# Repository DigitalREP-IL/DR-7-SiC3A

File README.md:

The Raspberry Pi, while a very capable and useful single-board computer, is often used with less than ideal power supplies. The Raspberry Pi monitors the incoming power and can both warn the user and slow down the system (clock throttling) to reduce power consumption. It is very common to have issues with SD Card corruption that can be traced back to power input issues as well. The simple solution presented by many kit vendors is to supply a power supply that provides 5.1V rather than the 5.0V nominal, in hopes that the extra voltage compensates for resistive losses in the cabling and by providing additional headroom over the 4.63V undervoltage warning level. However, a large contingent of would-be makers simply use a cellular phone charger and hope for the best. On older models, the power draw was somewhat lower but as of the latest 3B and 4 models the recommended supply current has risen to 3A.  Additionally, most USB chargers perform poorly at higher loads and may even drop out, hiccupping power to the SBC.

With this in mind, we’ve designed a DC/DC converter using the Vishay SiC-468 that can use common higher voltage power supplies such as a laptop “brick”, converting a 10-28V supply voltage to a very dependable 5V/3A output. The efficiency is typically above 92%, which is not only good for the environment but also keeps heat buildup to a minimum.

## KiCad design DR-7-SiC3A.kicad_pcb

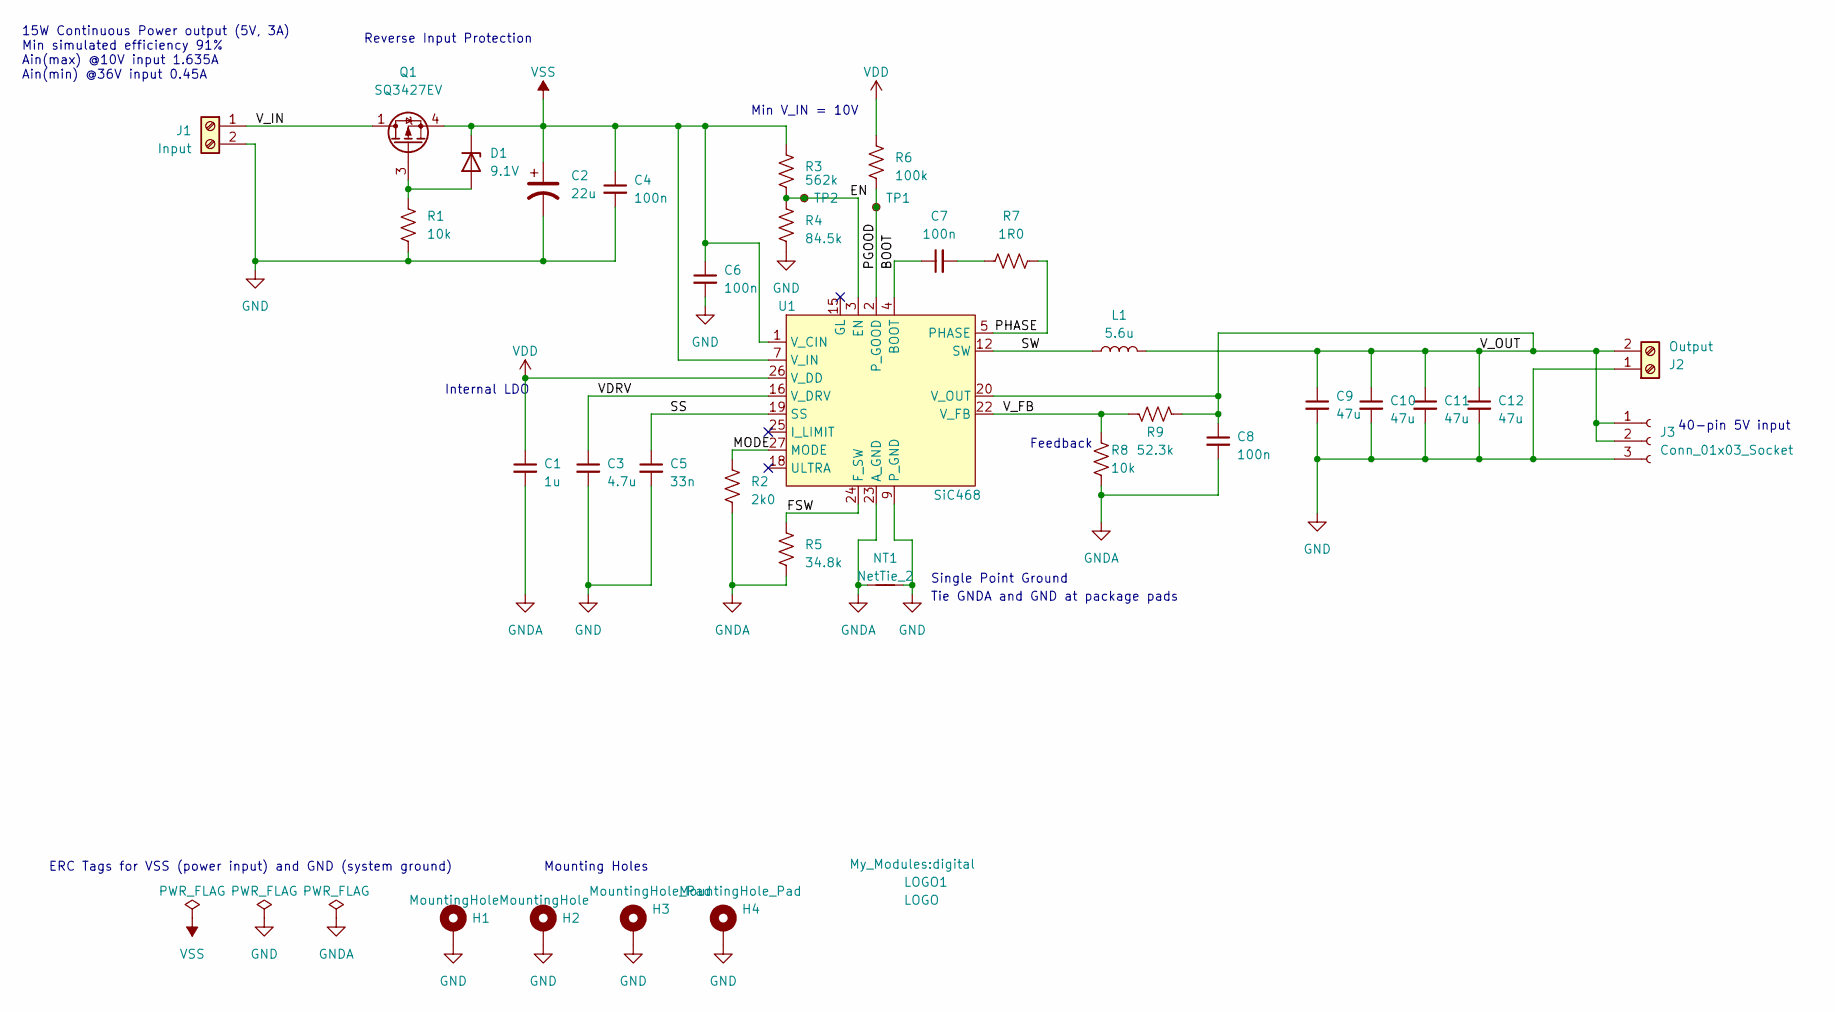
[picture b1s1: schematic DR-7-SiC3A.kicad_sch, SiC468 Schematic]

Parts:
C1: 1u; C_0603_1608Metric
C2: 22u; CP_Elec_6.3x5.8
C3: 4.7u; C_0603_1608Metric
C4: 100n; C_0805_2012Metric
C5: 33n; C_0603_1608Metric
C6: 100n; C_0603_1608Metric
C7, C8: 100n; C_0402_1005Metric
C9, C10, C11, C12: 47u; C_1210_3225Metric
D1: 9.1V; D_SMF; MPN BZG05C9V1-M3-08
H1, H2: MountingHole; MountingHole_2.7mm_M2.5_DIN965_Pad_TopBottom
H3, H4: MountingHole_Pad; MountingHole_2.7mm_M2.5_DIN965_Pad_TopBottom
J1: Input; TerminalBlock_Phoenix_MPT-0,5-2-2.54_1x02_P2.54mm_Horizontal
J2: Output; TerminalBlock_Phoenix_MPT-0,5-2-2.54_1x02_P2.54mm_Horizontal
J3: Conn_01x03_Socket; PinSocket_1x03_P2.54mm_Vertical
L1: 5.6u; IND_IHLP-4040DZ_VIS; MPN IHLP4040DZER5R6M01
LOGO1: LOGO; digital
NT1: NetTie_2; NetTie-2_SMD_Pad0.5mm
Q1: SQ3427EV; TSOP-6_1.65x3.05mm_P0.95mm; MPN SQ3427EV-T1_GE3
R1: 10k; R_0603_1608Metric
R2: 2k0; R_0603_1608Metric
R3: 562k; R_0603_1608Metric
R4: 84.5k; R_0603_1608Metric
R5: 34.8k; R_0603_1608Metric
R6: 100k; R_0603_1608Metric
R7: 1R0; R_0402_1005Metric
R8: 10k; R_0402_1005Metric
R9: 52.3k; R_0402_1005Metric
TP1, TP2: TestPoint_Small; TestPoint_THTPad_D1.5mm_Drill0.7mm
U1: SiC468; MLP55-27L; MPN SIC468ED-T1-GE3

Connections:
/BOOT: C7.1, U1.4 (BOOT)
/EN: R3.1, R4.2, TP2.1, U1.3 (EN)
/FSW: R5.2, U1.24 (F_SW)
/MODE: R2.2, U1.27 (MODE)
/PGOOD: R6.1, TP1.1, U1.2 (P_GOOD)
/PHASE: R7.2, U1.5 (PHASE), U1.6 (PHASE)
/SS: C5.1, U1.19 (SS)
/SW: L1.1, U1.12 (SW), U1.13 (SW), U1.14 (SW)
/VDRV: C3.1, U1.16 (V_DRV)
/V_FB: R8.2, R9.1, U1.22 (V_FB)
/V_IN: J1.1, Q1.1 (D), Q1.2 (D), Q1.5 (D), Q1.6 (D)
/V_OUT: C8.1, C9.1, C10.1, C11.1, C12.1, J2.2, J3.1, J3.2, L1.2, R9.2, U1.20 (V_OUT)
GND: C2.2, C3.2, C4.2, C5.2, C6.2, C9.2, C10.2, C11.2, C12.2, H1.1, H2.1, H3.1, H4.1, J1.2, J2.1, J3.3, NT1.2, R1.1, R4.1, U1.9 (P_GND), U1.10 (P_GND), U1.11 (P_GND), U1.17 (P_GND), U1.30 (P_GND)
GNDA: C1.2, C8.2, NT1.1, R2.1, R5.1, R8.1, U1.23 (A_GND), U1.28 (A_GND)
unnamed: C7.2, R7.1
unnamed: D1.2 (A), Q1.3 (G), R1.2
VDD: C1.1, R6.2, U1.26 (V_DD)
VSS: C2.1, C4.1, C6.1, D1.1 (K), Q1.4 (S), R3.2, U1.1 (V_CIN), U1.7 (V_IN), U1.8 (V_IN), U1.29 (V_IN)

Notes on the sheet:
Internal LDO
ERC Tags for VSS (power input) and GND (system ground)
Reverse Input Protection
Feedback
Single Point Ground
Tie GNDA and GND at package pads
15W Continuous Power output (5V, 3A) Min simulated efficiency 91% Ain(max) @10V input 1.635A Ain(min) @36V input 0.45A
Min V_IN = 10V
Mounting Holes
40-pin 5V input

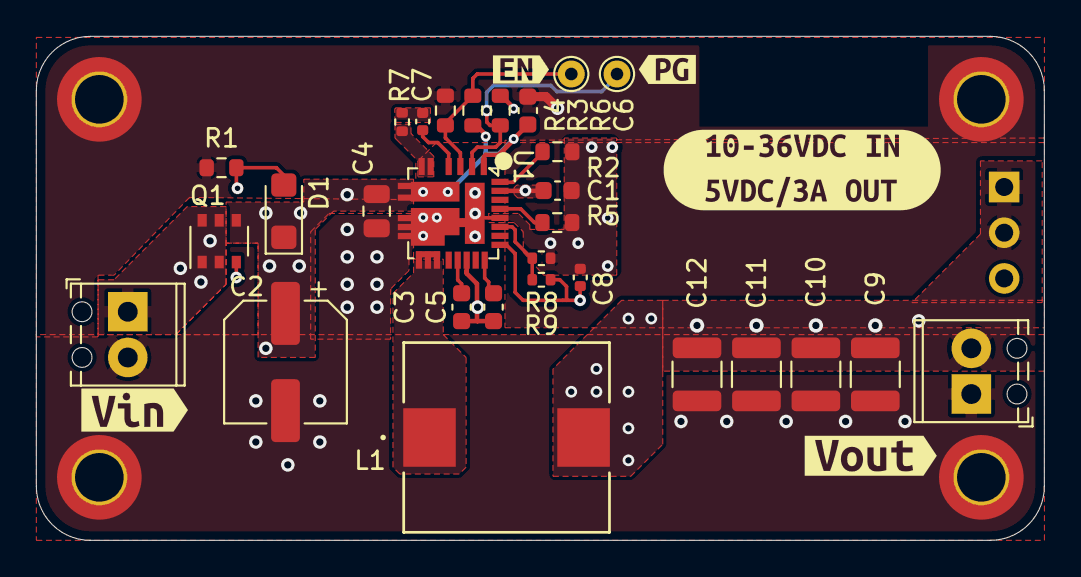
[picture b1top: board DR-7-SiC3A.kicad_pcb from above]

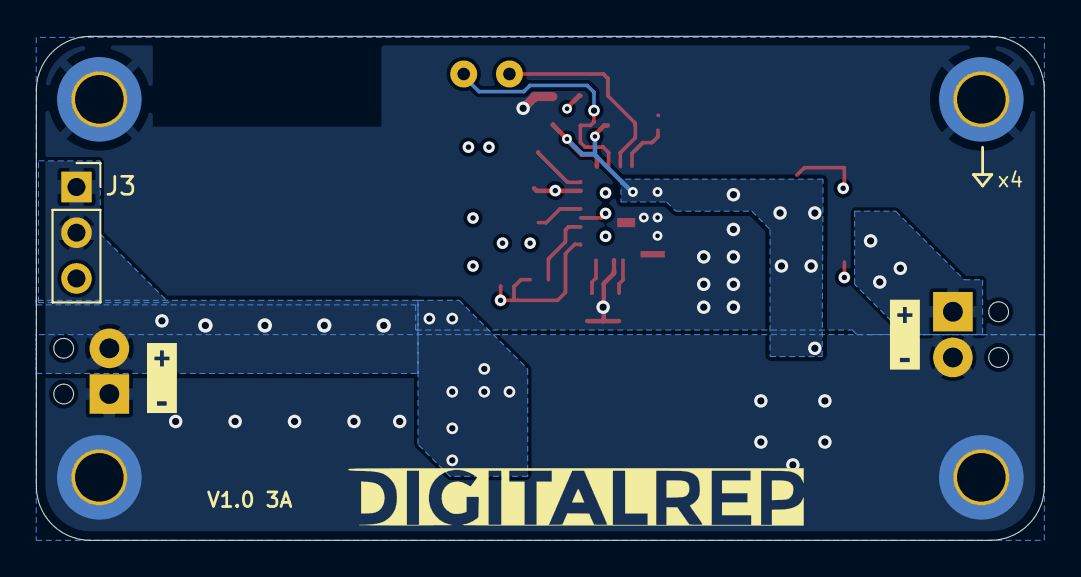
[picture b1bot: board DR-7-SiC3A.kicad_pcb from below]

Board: 4 copper layers, 56.0 x 28.0 mm, 43 parts (4 on the bottom side), 18 nets.

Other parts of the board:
kibuzzard-64C2B50E: G***; kibuzzard-64C2B50E
kibuzzard-64C2B51C: G***; kibuzzard-64C2B51C
kibuzzard-64C2B535: G***; kibuzzard-64C2B535
kibuzzard-64C2B591: G***; kibuzzard-64C2B591
kibuzzard-64469095, kibuzzard-64469095#2: G***; kibuzzard-64469095
kibuzzard-65242275: G***; kibuzzard-65242275

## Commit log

2024-03-15 First commit of 3A design prior to engineering eval build. Has passed Vishay initial review.
